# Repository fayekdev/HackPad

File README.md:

# **.devPAD**

An Elevated "SteamDeck" for developpers with fully customizable controls across many programs. I made it to make my life easier by having all of the most used tools and a way to properly move in CAD using the joystick in the middle. The e-ink screen is used as clock and a to-do list and could display the current media, volume level, microphone status and temperature.

***the tech stack***

## Screenshots

## *THE CODE*

The code is still incomplete but still has ~80% functionality(only a few minor changes to make)

Currently working on the hardware problems so it is on delay

## *How was it made*  

- I designed the PCB in KiCAD and exported to Fusion to model the Case.

- The case was modeled and the components too to ensure the fit is correct

- Printed the first version 

- Fixed the errors in V1 and added a few features. 

- The PCB arrived and all components were test fit

- Began soldering the PCB 

- Fixed the errors I had made and uploaded a few test sketches.

- Test sketches were success and I tested the production code

- Production code worked out fine with a few problems

- A wire connected the screen to the microcontroller snapped and when trying to fix it a short-circuit happened and probably caused the microcontroller to malfunction.

*(The device only worked for 30 minutes or so before breaking)*

## *AI disclosure*

- AI was used as a research tool where I gave it all my requirements in one and it generated some sort of documentation that was held in it's context window so that when I ask a question or have a concern it automatically gives the answer I need instead of losing a ton of time researching myself

- Another usecase is the few errors I stumble upon that I spent a ton of time trying to fix I give to AI to give me a suggestion on how to fix it 

## Installation

Install the .devPAD desktop app --> 

Upload the **main.ino** sketch to the microcontroller

**SCREENSHOTS OF THE APP**

## BOM

| Component    | Qty |
| ---------    | --: |
|Xiao ESP32 C3                              |   1  |
|  Keycaps                                  |  14  |
|We-Act studio 2.9" E-ink screen             |   1  |
| M2x6 screws                               |   8  |
|MX-Cherr Keyswitches                       |    14  |
|     1N4148 diodes       |  16   |
|    Rotary encoder          |  1   |
|   Joystick           |   1  |
|     Wire         |   (as much as you need)  |
|    SN74HC595N          |  1   |
|PCB|  1|

**TOOLS**

- Access to a 3D printer & filament
- Soldering tools 
- Wire strippers
- USB-C wire
- Arduino IDE

## Assembly GUIDE

1. Print all of the components. The face plate cover is optional (you should glue it if you want to use it)
---
2. Solder the first diode (under the joystick) upside down then solder the rest upright.
---
3. Solder the Joystick in its respective place but make sure it is properly level.
---
4. Solder the SN74HC595 and the Xiao ESP32 C3.
---
5. Solder all of the keyswitches.
---
7. Screw in the encoder and seat in the screen (if you want to make sure it's even more secure, use some tape instead of using the support beam).
---
8. Solder all of the encoder wires from the bottom and solder them to the encoder.
---
9. Solder the screen using it's respective connections using the 
schematic as a reference PS: The purple wire is not needed and the orange one should be wired up to the RST switch.
---
10. Seat the PCB and screw it in.
---
11. Close up the top plate being careful that the wires don't interfere with the USB port. You could put the USB-C wire in and close up the top plate to keep the wires from interfering
---
12. Add the joystick, the encoder knob and the 14 keycaps.
---
13. Upload the **main.ino** sketch via the Arduino IDE and run the ".devPAD" app
---

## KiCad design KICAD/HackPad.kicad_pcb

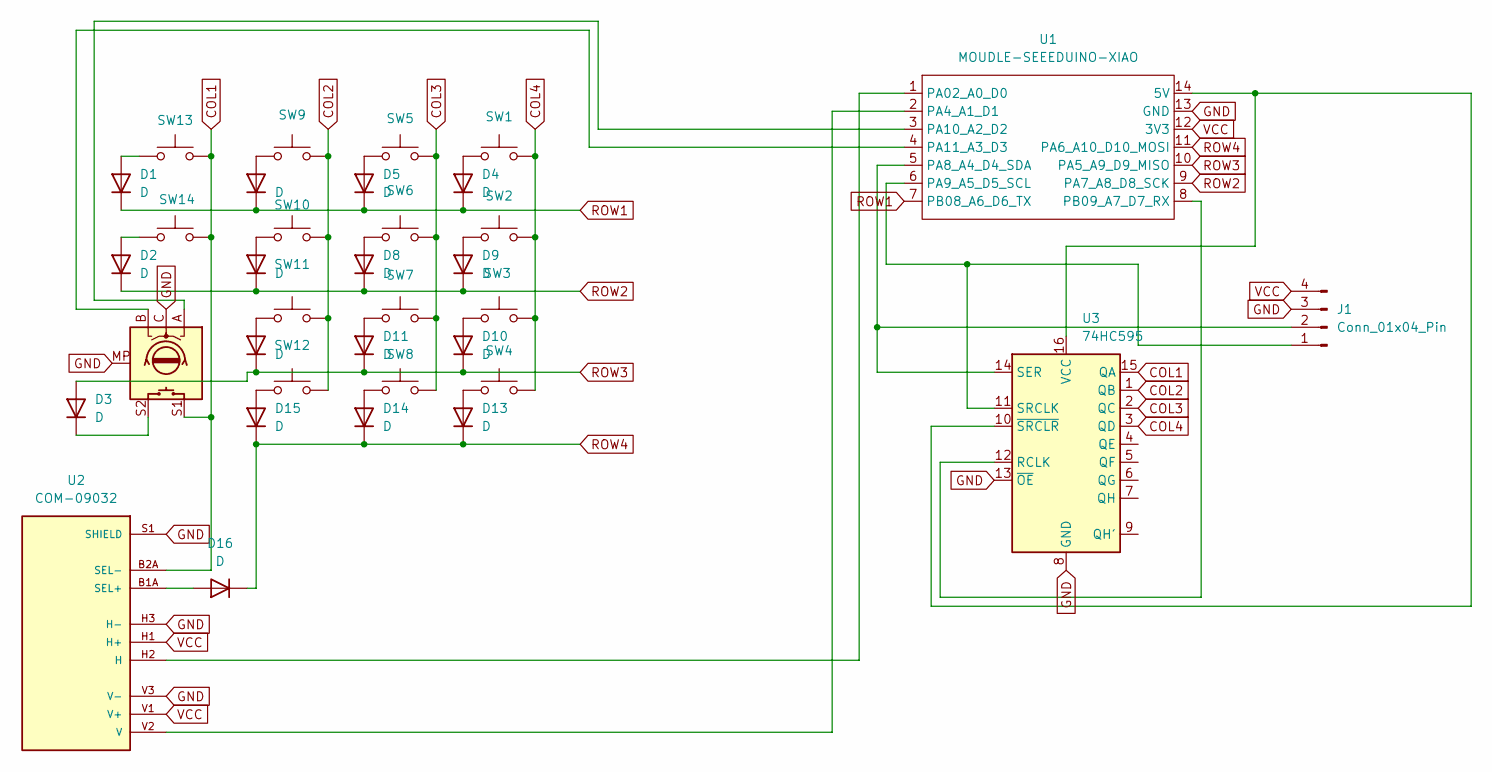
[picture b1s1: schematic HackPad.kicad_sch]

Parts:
D1, D2, D3, D4, D5, D6, D7, D8, D9, D10, D11, D12, D13, D14, D15, D16: D; D_DO-35_SOD27_P7.62mm_Horizontal
J1: Conn_01x04_Pin; PinHeader_1x04_P2.54mm_Vertical
SW1, SW2, SW3, SW4, SW5, SW6, SW7, SW8, SW9, SW10, SW11, SW12, SW13, SW14: SW_Push; SW_Cherry_MX_1.00u_PCB
SW15: RotaryEncoder_Switch_MP; RotaryEncoder_Alps_EC11E-Switch_Vertical_H20mm
U1: MOUDLE-SEEEDUINO-XIAO; MCU_Seeed_ESP32C3
U2: COM-09032; XDCR_COM-09032; PARTREV N/A
U3: 74HC595; DIP-16_W7.62mm

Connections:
COL1: SW13.2, SW14.2, SW15.S1, U2.B2A (SEL-), U3.15 (QA)
COL2: SW9.2, SW10.2, SW11.2, SW12.2, U3.1 (QB)
COL3: SW5.2, SW6.2, SW7.2, SW8.2, U3.2 (QC)
COL4: SW1.2, SW2.2, SW3.2, SW4.2, U3.3 (QD)
GND: J1.3, SW15.C, SW15.MP, U1.13 (GND), U2.H3 (H-), U2.S1 (SHIELD), U2.S2 (SHIELD), U2.S3 (SHIELD), U2.S4 (SHIELD), U2.V3 (V-), U3.8 (GND), U3.13 (~OE)
unnamed: D1.2 (A), SW13.1
unnamed: D2.2 (A), SW14.1
unnamed: D3.1 (K), SW15.S2
unnamed: D4.2 (A), SW1.1
unnamed: D5.2 (A), SW5.1
unnamed: D6.2 (A), SW9.1
unnamed: D7.2 (A), SW10.1
unnamed: D8.2 (A), SW6.1
unnamed: D9.2 (A), SW2.1
unnamed: D10.2 (A), SW3.1
unnamed: D11.2 (A), SW7.1
unnamed: D12.2 (A), SW11.1
unnamed: D13.2 (A), SW4.1
unnamed: D14.2 (A), SW8.1
unnamed: D15.2 (A), SW12.1
unnamed: D16.2 (A), U2.B1A (SEL+)
unnamed: J1.1, U1.6 (PA9_A5_D5_SCL), U3.11 (SRCLK)
unnamed: J1.2, U1.5 (PA8_A4_D4_SDA), U3.14 (SER)
unnamed: U1.14 (5V), U3.10 (~SRCLR), U3.16 (VCC)
unnamed: U1.1 (PA02_A0_D0), U2.H2 (H)
unnamed: U1.2 (PA4_A1_D1), U2.V2 (V)
unnamed: SW15.A, U1.3 (PA10_A2_D2)
unnamed: SW15.B, U1.4 (PA11_A3_D3)
unnamed: U1.8 (PB09_A7_D7_RX), U3.12 (RCLK)
ROW1: D1.1 (K), D4.1 (K), D5.1 (K), D6.1 (K), U1.7 (PB08_A6_D6_TX)
ROW2: D2.1 (K), D7.1 (K), D8.1 (K), D9.1 (K), U1.9 (PA7_A8_D8_SCK)
ROW3: D3.2 (A), D10.1 (K), D11.1 (K), D12.1 (K), U1.10 (PA5_A9_D9_MISO)
ROW4: D13.1 (K), D14.1 (K), D15.1 (K), D16.1 (K), U1.11 (PA6_A10_D10_MOSI)
VCC: J1.4, U1.12 (3V3), U2.H1 (H+), U2.V1 (V+)

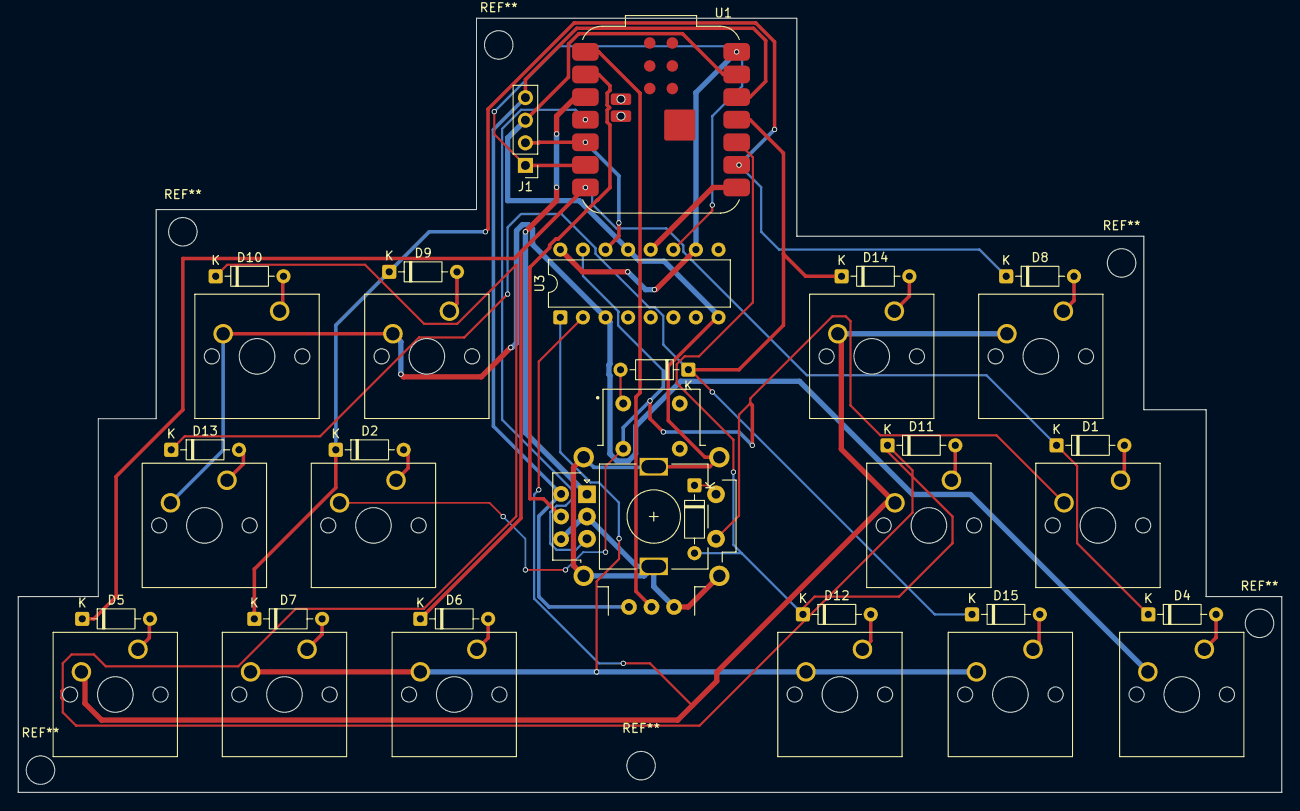
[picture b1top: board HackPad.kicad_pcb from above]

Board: 2 copper layers, 142.0 x 87.0 mm, 35 parts (0 on the bottom side), 34 nets.
